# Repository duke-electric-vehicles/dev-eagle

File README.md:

# dev-eagle
Board files for Duke Electric Vehicles

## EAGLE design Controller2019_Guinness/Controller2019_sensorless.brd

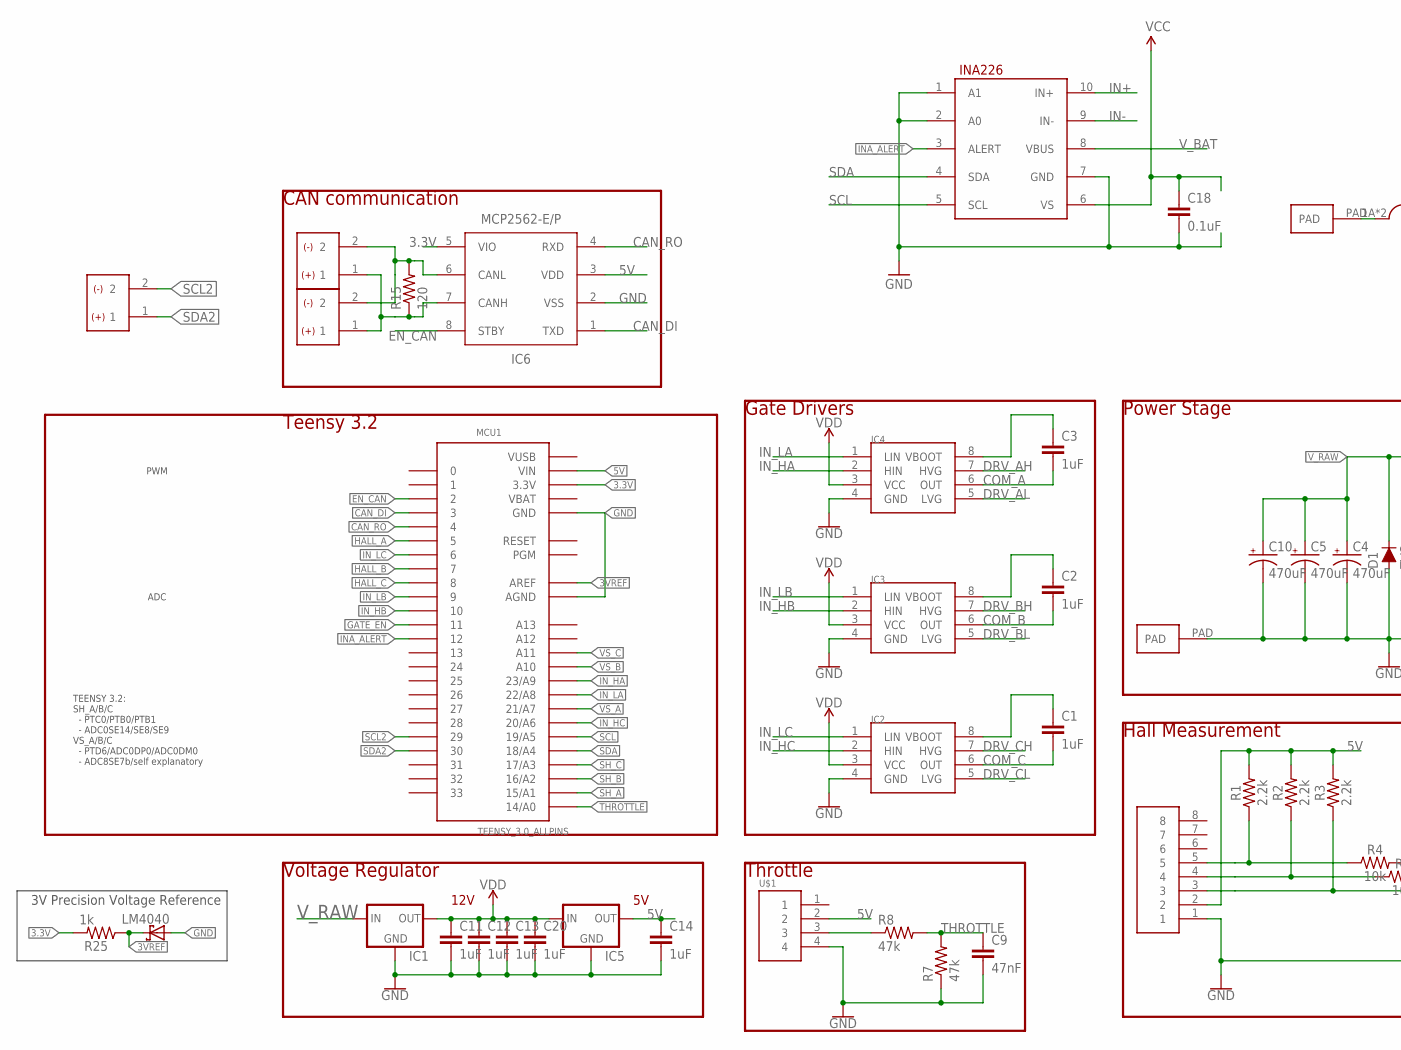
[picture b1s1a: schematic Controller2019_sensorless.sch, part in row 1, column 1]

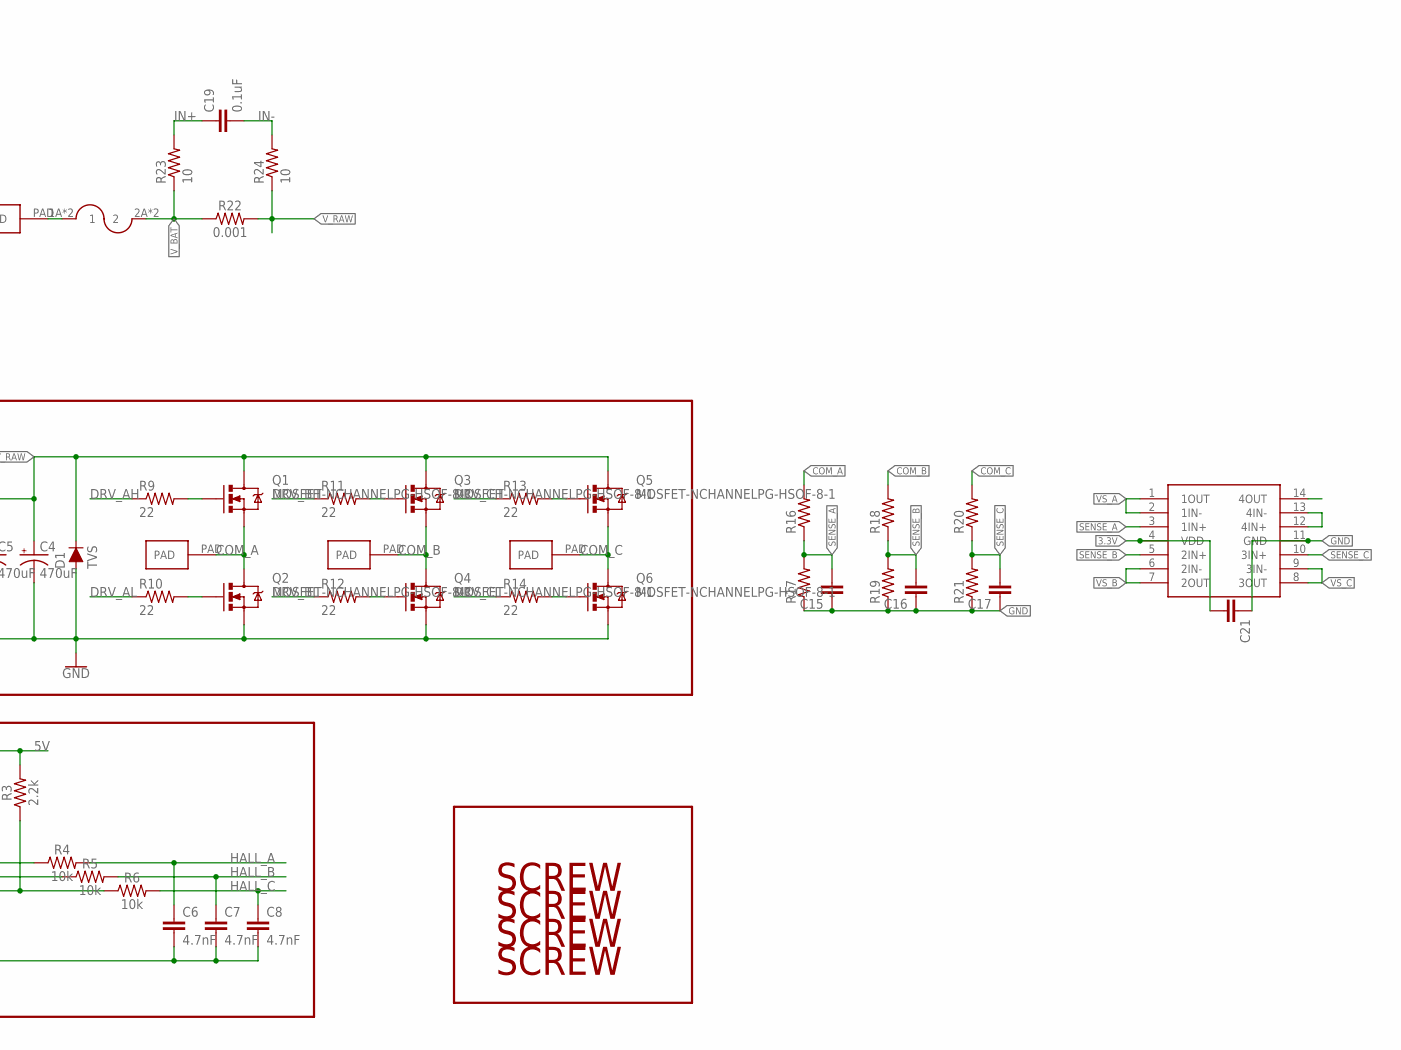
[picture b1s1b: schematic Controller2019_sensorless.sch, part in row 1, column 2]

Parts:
C1, C2, C3, C11, C12, C13, C14, C20: 1uF; CAP-PTH-SMALL-KIT
C4, C5, C10: 470uF; CPOL-RADIAL-5MM-10MM
C6, C7, C8: 4.7nF; 0603-CAP
C9: 47nF; 0603-CAP
C15, C16, C17, C21: CAP0603-CAP; 0603-CAP
C18, C19: 0.1uF; 0603-CAP
CAN1, CAN2: HEADER2; 2PINVALULOK
D1: TVS; DIODE-1N4001
I2C: HEADER2; 2PINVALULOK
IC1: V_REG_78XX; V78W_BACKWARDS
IC2, IC3, IC4: L6387EDIP8; DIP762W53P254L1092H508Q8B
IC5: V_REG_78XXV78W; V78W
IC6: MCP2562-E/P; PDIP8_300MC
IC7: INA226; PSOP-10
J3: FUSE; AUTO_FUSE
MCU1: TEENSY_3.0_ALLPINS
Q1, Q2, Q3, Q4, Q5, Q6: MOSFET-NCHANNELPG-HSOF-8-1; PG-HSOF-8-1
R1, R2, R3: 2.2k; 0603-RES
R4, R5, R6: 10k; 0603-RES
R7, R8: 47k; 0603-RES
R9, R10, R11, R12, R13, R14: 22; 0603-RES
R15: 120; 0603-RES
R16, R17, R18, R19, R20, R21: RESISTOR0603-RES; 0603-RES
R22: 0.001; R2512
R23, R24: 10; 0603-RES
R25: 1k; 0603-RES
U$1: HEADER4VALULOK; 4PINVALULOK
U$2: OPAMP_QUAD; TSSOP-14
U$4, U$5, U$6, U$7, U$8: PAD
U$10, U$11, U$12, U$13: SCREW; M3HOLE
U$14: HEADER8; 8PINVALULOK
U$15: LM4040; SOT23-3

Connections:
3.3V: C21.2, IC6.5 (VIO), MCU1.3.3V, MCU1.3.3V1 (3.3V), MCU1.3.3V2 (3.3V), R25.2, U$2.4 (VDD)
3VREF: MCU1.AREF, R25.1, U$15.1 (C)
5V: C14.1, IC5.OUT, IC6.3 (VDD), MCU1.VIN, R1.2, R2.2, R3.2, U$1.2, U$14.2
CANH: CAN1.1, CAN2.1, IC6.7 (CANH), R15.1
CANL: CAN1.2, CAN2.2, IC6.6 (CANL), R15.2
CAN_DI: IC6.1 (TXD), MCU1.3
CAN_RO: IC6.4 (RXD), MCU1.4
COM_A: C3.2, IC4.6 (OUT), Q1.S, Q2.D, R16.2, U$6.PAD
COM_B: C2.2, IC3.6 (OUT), Q3.S, Q4.D, R18.2, U$7.PAD
COM_C: C1.2, IC2.6 (OUT), Q5.S, Q6.D, R20.2, U$8.PAD
DRV_AH: IC4.7 (HVG), R9.1
DRV_AL: IC4.5 (LVG), R10.1
DRV_BH: IC3.7 (HVG), R11.1
DRV_BL: IC3.5 (LVG), R12.1
DRV_CH: IC2.7 (HVG), R13.1
DRV_CL: IC2.5 (LVG), R14.1
EN_CAN: IC6.8 (STBY), MCU1.2
GATE_EN: MCU1.11
GND: C4.-, C5.-, C6.2, C7.2, C8.2, C9.2, C10.-, C11.2, C12.2, C13.2, C14.2, C15.1, C16.1, C17.1, C18.2, C20.2, C21.1, D1.A, IC1.GND, IC2.4 (GND), IC3.4 (GND), IC4.4 (GND), IC5.GND, IC6.2 (VSS), IC7.1 (A1), IC7.2 (A0), IC7.7 (GND), MCU1.AGND, MCU1.GND, MCU1.GND1 (GND), MCU1.GND2 (GND), Q2.S, Q4.S, Q6.S, R7.1, R17.1, R19.1, R21.1, U$1.4, U$2.11 (GND), U$5.PAD, U$14.1, U$15.2 (A)
HALL_A: C6.1, MCU1.5, R4.2
HALL_B: C7.1, MCU1.7, R5.2
HALL_C: C8.1, MCU1.8, R6.2
IN+: C19.1, IC7.10 (IN+), R23.2
IN-: C19.2, IC7.9 (IN-), R24.2
INA_ALERT: IC7.3 (ALERT), MCU1.12
IN_HA: IC4.2 (HIN), MCU1.23/A9
IN_HB: IC3.2 (HIN), MCU1.10
IN_HC: IC2.2 (HIN), MCU1.20/A6
IN_LA: IC4.1 (LIN), MCU1.22/A8
IN_LB: IC3.1 (LIN), MCU1.9
IN_LC: IC2.1 (LIN), MCU1.6
unnamed: C1.1, IC2.8 (VBOOT)
unnamed: R3.1, R6.1, U$14.3
unnamed: C2.1, IC3.8 (VBOOT)
unnamed: R2.1, R5.1, U$14.4
unnamed: C3.1, IC4.8 (VBOOT)
unnamed: R1.1, R4.1, U$14.5
unnamed: R8.1, U$1.3
unnamed: Q1.G, R9.2
unnamed: Q2.G, R10.2
unnamed: Q3.G, R11.2
unnamed: Q4.G, R12.2
unnamed: Q5.G, R13.2
unnamed: Q6.G, R14.2
unnamed: U$2.12 (4IN+), U$2.13 (4IN-)
SCL: IC7.5 (SCL), MCU1.19/A5
SCL2: I2C.2, MCU1.29
SDA: IC7.4 (SDA), MCU1.18/A4
SDA2: I2C.1, MCU1.30
SENSE_A: C15.2, R16.1, R17.2, U$2.3 (1IN+)
SENSE_B: C16.2, R18.1, R19.2, U$2.5 (2IN+)
SENSE_C: C17.2, R20.1, R21.2, U$2.10 (3IN+)
SH_A: MCU1.15/A1
SH_B: MCU1.16/A2
SH_C: MCU1.17/A3
THROTTLE: C9.1, MCU1.14/A0, R7.2, R8.2
VBAT: MCU1.VBAT
VCC: C18.1, IC7.6 (VS)
VDD: C11.1, C12.1, C13.1, C20.1, IC1.OUT, IC2.3 (VCC), IC3.3 (VCC), IC4.3 (VCC), IC5.IN
VS_A: MCU1.21/A7, U$2.1 (1OUT), U$2.2 (1IN-)
VS_B: MCU1.A10, U$2.6 (2IN-), U$2.7 (2OUT)
VS_C: MCU1.A11, U$2.8 (3OUT), U$2.9 (3IN-)
VUSB: MCU1.VUSB
V_BAT: IC7.8 (VBUS), J3.2A (2), J3.2B (2), R22.1, R23.1
V_PREFUSE: J3.1A (1), J3.1B (1), U$4.PAD
V_RAW: C4.+, C5.+, C10.+, D1.C, IC1.IN, Q1.D, Q3.D, Q5.D, R22.2, R24.1

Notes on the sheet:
Power Stage
Hall Measurement
Gate Drivers
Throttle
Teensy 3.2
Voltage Regulator
12V
CAN communication
PWM
ADC
TEENSY 3.2: SH_A/B/C - PTC0/PTB0/PTB1 - ADC0SE14/SE8/SE9 VS_A/B/C - PTD6/ADC0DP0/ADC0DM0 - ADC8SE7b/self explanatory
3V Precision Voltage Reference

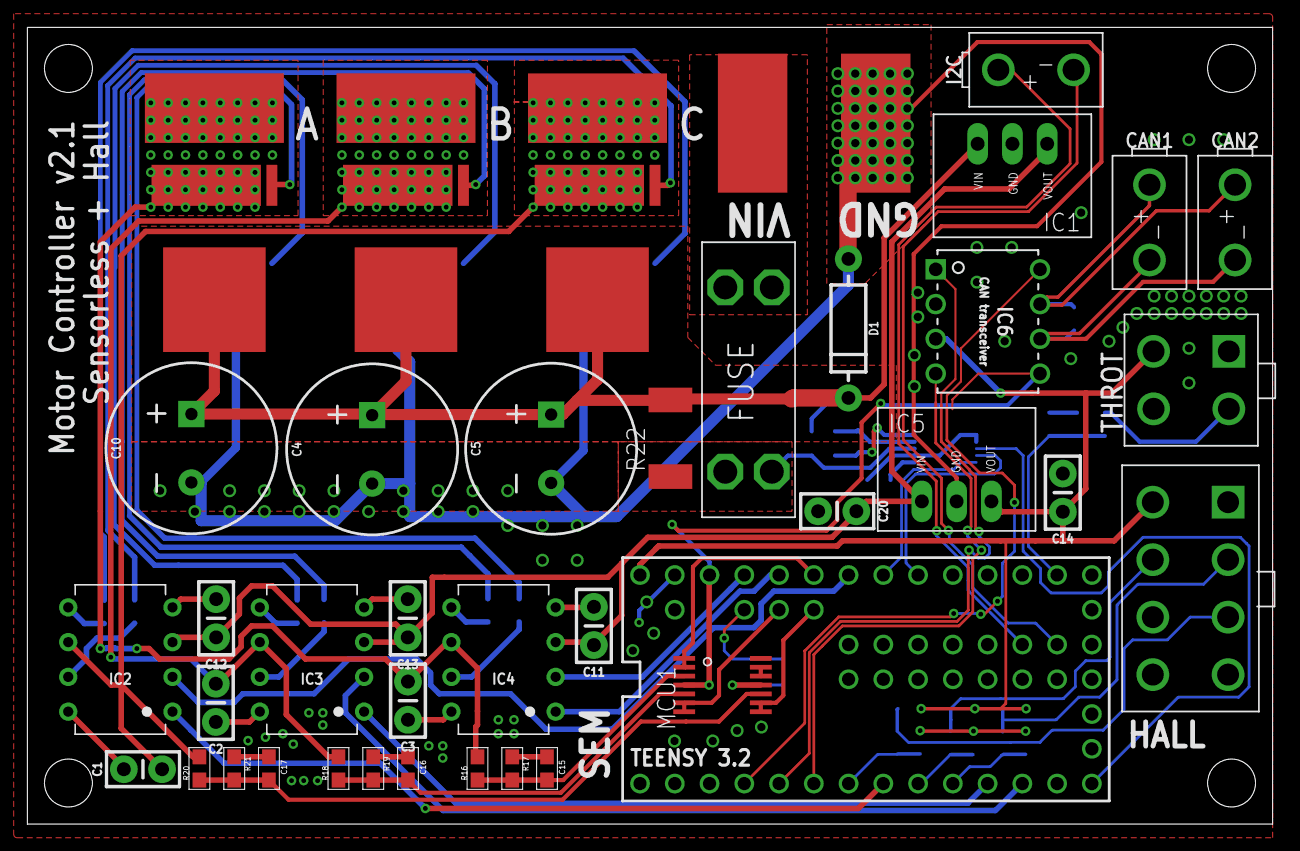
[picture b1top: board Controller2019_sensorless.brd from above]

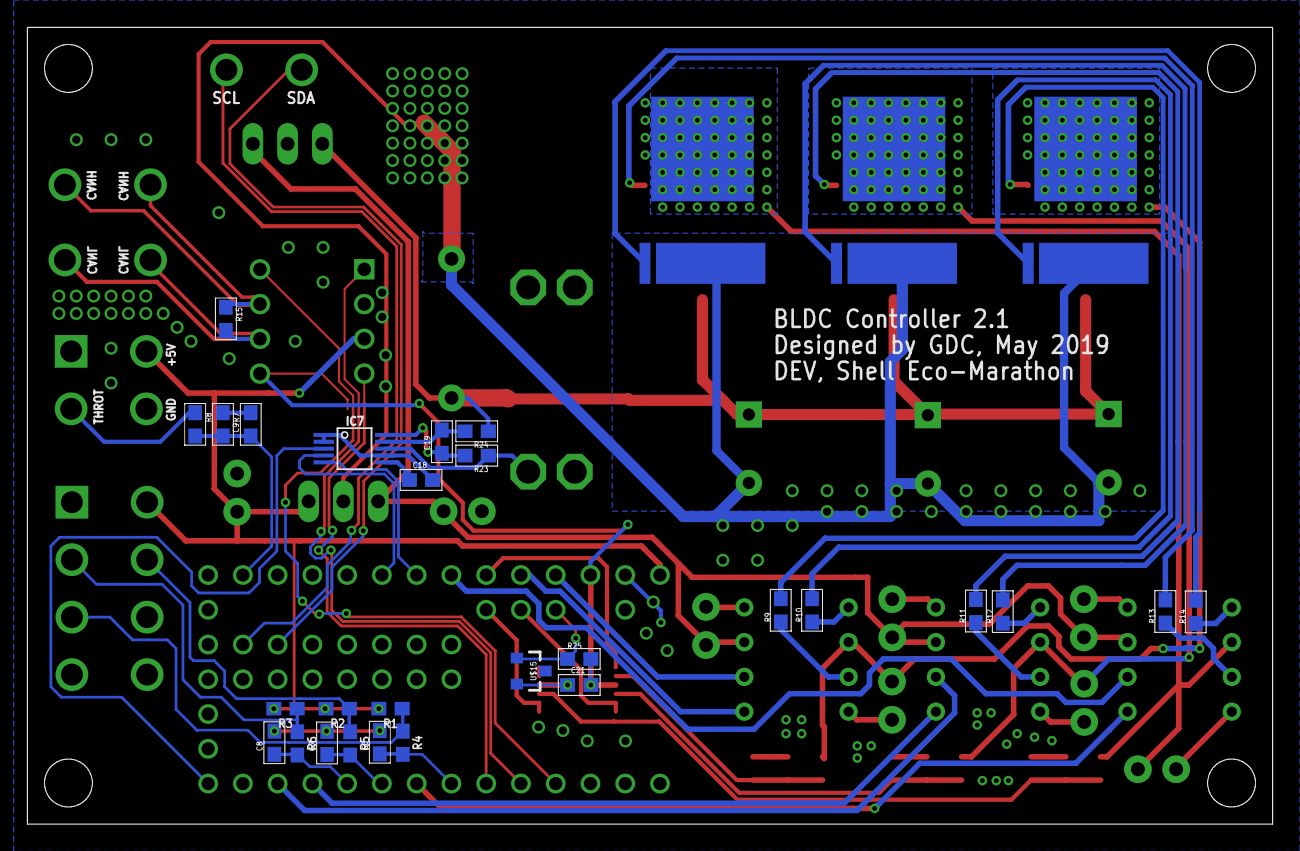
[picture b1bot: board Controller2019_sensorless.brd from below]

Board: 2 copper layers, 91.0 x 58.2 mm, 79 parts (31 on the bottom side), 60 nets.

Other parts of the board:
U$3: DEV

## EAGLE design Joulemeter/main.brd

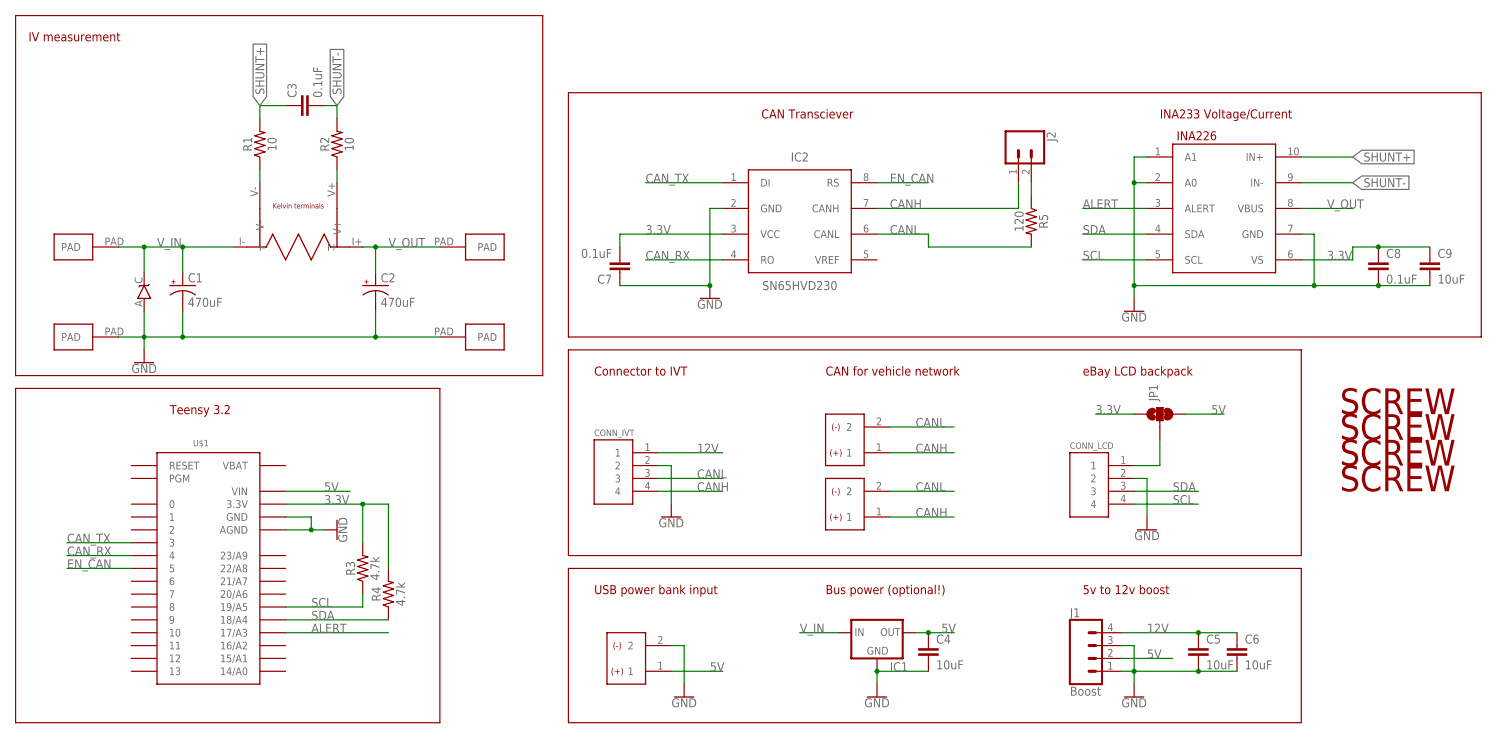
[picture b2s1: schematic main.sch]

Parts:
C1, C2: 470uF; CPOL-RADIAL-5MM-10MM
C3, C7, C8: 0.1uF; 0603
C4, C5, C6, C9: 10uF; 1210
CONN_IVT: LCD; 4PINVALULOK
CONN_LCD: LCD; 4PINVALULOK
IC1: V_REG_78XX; V78W_BACKWARDS
IC2: SN65HVD230; SOIC127P650X175-8
J1: Boost; 1X04_LONGPADS
J2: CONN_02; 1X02
JP1: JUMPER-SMT_3_1-NC_TRACE_SILK; SMT-JUMPER_3_1-NC_TRACE_SILK
R1, R2: 10; 0603
R3, R4: 4.7k; 0603
R5: 120; 0603
U$1: TEENSY_3.0_BASIC
U$2: 5mOhm; 2512_KELVIN
U$3, U$4, U$7, U$8: PAD
U$5: INA226; PSOP-10
U$6: TVS_UNIDO-214AC; DO-214AC
U$9, U$10: HEADER2; 2PINVALULOK
U$11, U$12, U$13, U$14: SCREW; M3HOLE
USB_PWR: USB_PWR; 2PINVALULOK

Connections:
3.3V: C7.2, C8.1, C9.1, IC2.3 (VCC), JP1.1, R3.2, R4.2, U$1.3.3V, U$1.3.3V1 (3.3V), U$5.6 (VS)
5V: C4.1, IC1.OUT, J1.2, JP1.3, U$1.VIN, USB_PWR.1
12V: C5.1, C6.1, CONN_IVT.1, J1.4
ALERT: U$1.17/A3, U$5.3 (ALERT)
CANH: CONN_IVT.4, IC2.7 (CANH), J2.1, U$9.1, U$10.1
CANL: CONN_IVT.3, IC2.6 (CANL), R5.2, U$9.2, U$10.2
CAN_RX: IC2.4 (RO), U$1.4
CAN_TX: IC2.1 (DI), U$1.3
EN_CAN: IC2.8 (RS), U$1.5
GND: C1.-, C2.-, C4.2, C5.2, C6.2, C7.1, C8.2, C9.2, CONN_IVT.2, CONN_LCD.2, IC1.GND, IC2.2 (GND), J1.1, J1.3, U$1.AGND, U$1.GND, U$1.GND1 (GND), U$4.PAD, U$5.1 (A1), U$5.2 (A0), U$5.7 (GND), U$6.A, U$8.PAD, USB_PWR.2
unnamed: R1.1, U$2.V-
unnamed: R2.1, U$2.V+
unnamed: CONN_LCD.1, JP1.2
unnamed: J2.2, R5.1
SCL: CONN_LCD.4, R3.1, U$1.19/A5, U$5.5 (SCL)
SDA: CONN_LCD.3, R4.1, U$1.18/A4, U$5.4 (SDA)
SHUNT+: C3.1, R1.2, U$5.10 (IN+)
SHUNT-: C3.2, R2.2, U$5.9 (IN-)
VBAT: U$1.VBAT
V_IN: C1.+, IC1.IN, U$2.I-, U$3.PAD, U$6.C
V_OUT: C2.+, U$2.I+, U$5.8 (VBUS), U$7.PAD

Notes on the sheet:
Bus power (optional!)
5v to 12v boost
USB power bank input
Connector to IVT
CAN for vehicle network
eBay LCD backpack
IV measurement
CAN Transciever
INA233 Voltage/Current
Teensy 3.2

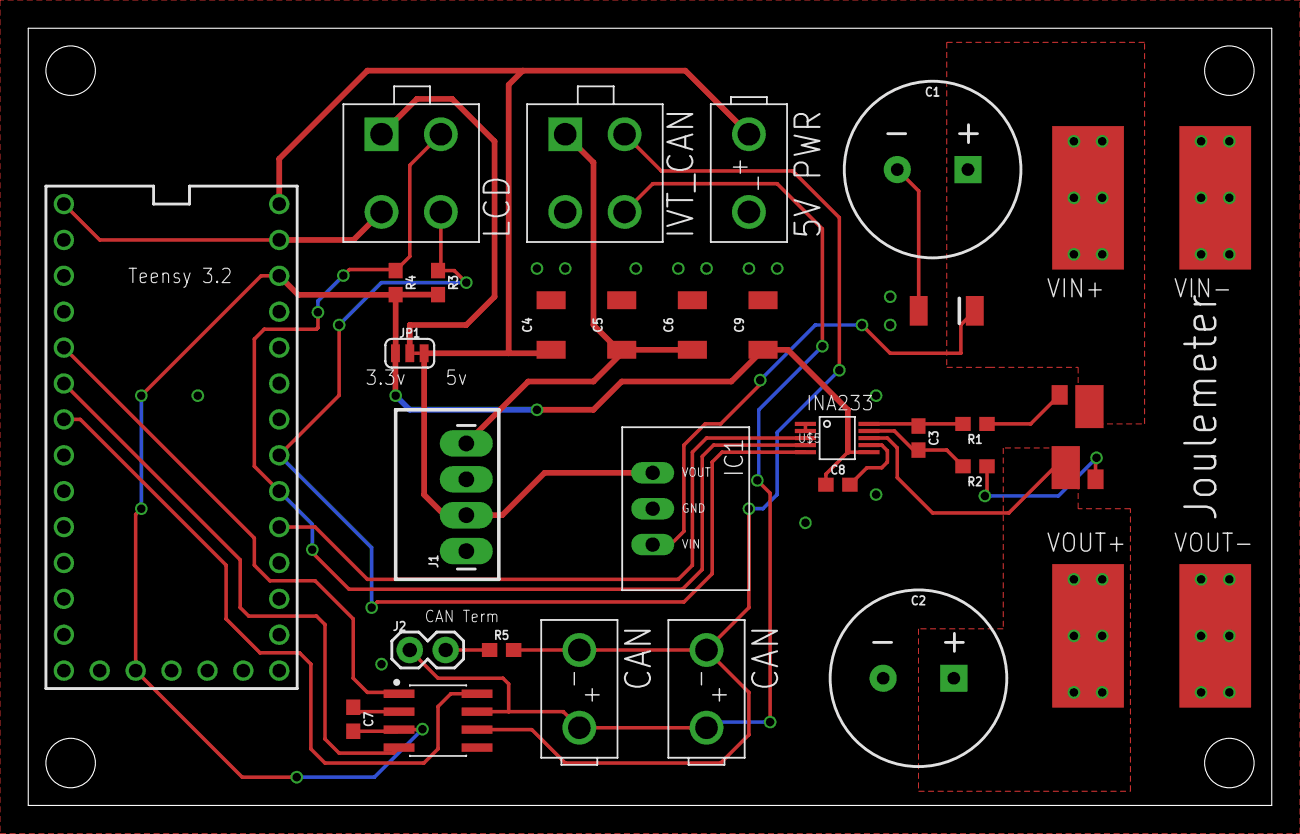
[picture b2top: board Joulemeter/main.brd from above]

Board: 2 copper layers, 88.0 x 55.0 mm, 36 parts (0 on the bottom side), 20 nets.

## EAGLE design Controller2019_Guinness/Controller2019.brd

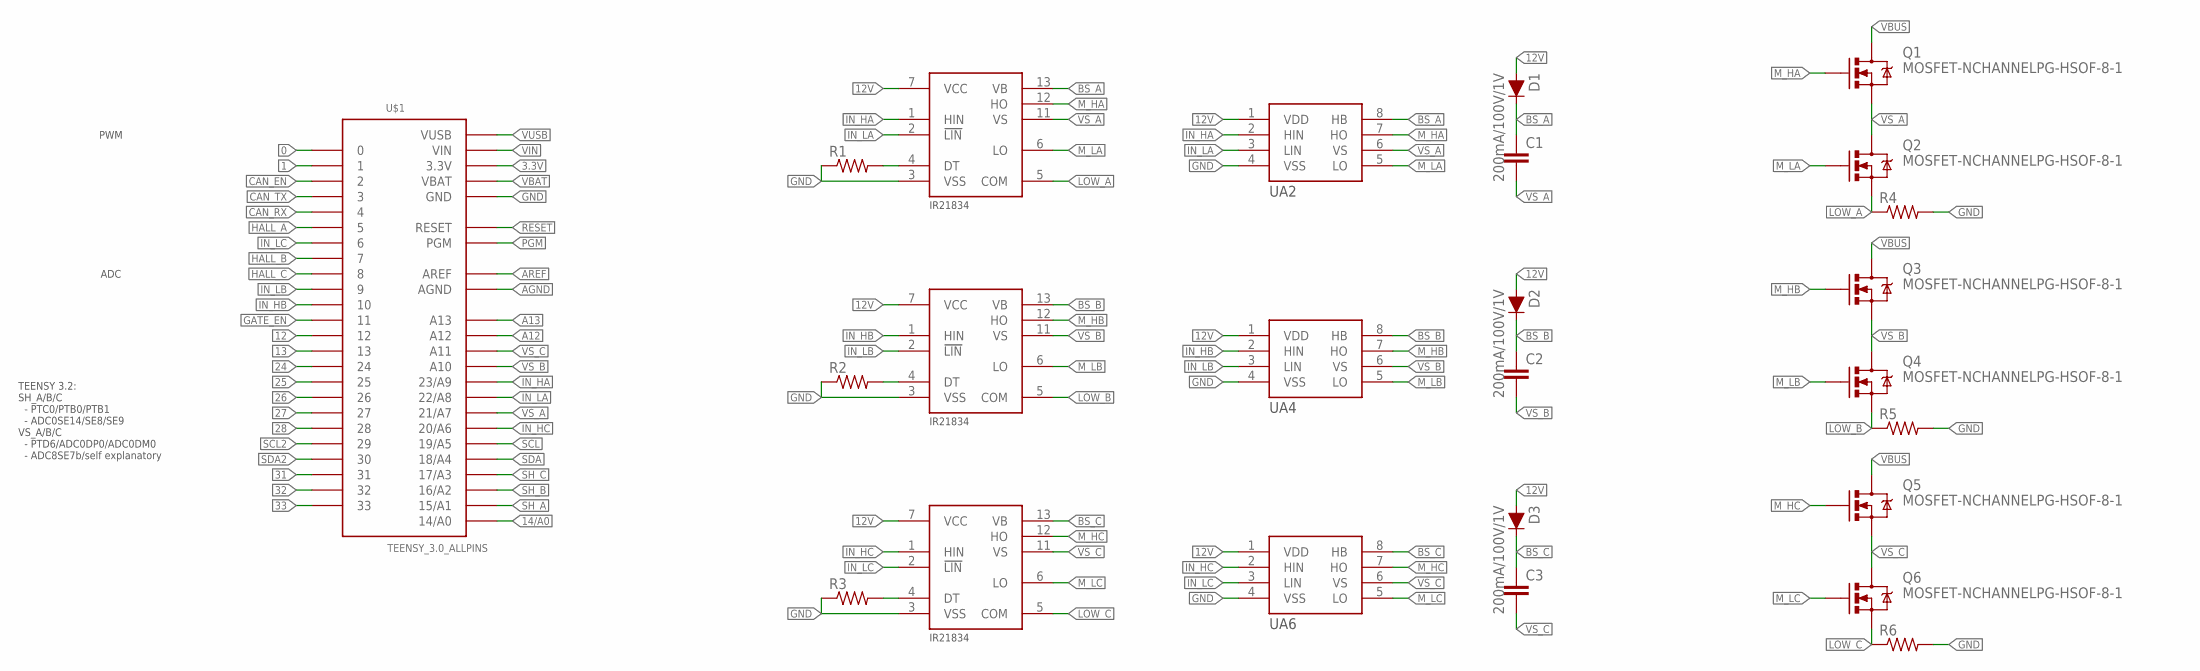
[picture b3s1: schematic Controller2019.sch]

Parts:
C1, C2, C3: CAP0603-CAP; 0603-CAP
D1, D2, D3: 200mA/100V/1V; DIODE-1N4148
Q1, Q2, Q3, Q4, Q5, Q6: MOSFET-NCHANNELPG-HSOF-8-1; PG-HSOF-8-1
R1, R2, R3: RESISTOR0603-RES; 0603-RES
R4, R5, R6: RESISTOR2512; R2512
U$1: TEENSY_3.0_ALLPINS
UA1, UA3, UA5: IR21834; SO14
UA2, UA4, UA6: GATEDRIVER_IND_ISL6700; SOIC8

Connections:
0: U$1.0
1: U$1.1
3.3V: U$1.3.3V, U$1.3.3V1 (3.3V), U$1.3.3V2 (3.3V)
12: U$1.12
12V: D1.A, D2.A, D3.A, UA1.7 (VCC), UA2.1 (VDD), UA3.7 (VCC), UA4.1 (VDD), UA5.7 (VCC), UA6.1 (VDD)
13: U$1.13
14/A0: U$1.14/A0
24: U$1.24
25: U$1.25
26: U$1.26
27: U$1.27
28: U$1.28
31: U$1.31
32: U$1.32
33: U$1.33
A12: U$1.A12
A13: U$1.A13
AGND: U$1.AGND
AREF: U$1.AREF
BS_A: C1.1, D1.C, UA1.13 (VB), UA2.8 (HB)
BS_B: C2.1, D2.C, UA3.13 (VB), UA4.8 (HB)
BS_C: C3.1, D3.C, UA5.13 (VB), UA6.8 (HB)
CAN_EN: U$1.2
CAN_RX: U$1.4
CAN_TX: U$1.3
GATE_EN: U$1.11
GND: R1.1, R2.1, R3.1, R4.2, R5.2, R6.2, U$1.GND, U$1.GND1 (GND), U$1.GND2 (GND), UA1.3 (VSS), UA2.4 (VSS), UA3.3 (VSS), UA4.4 (VSS), UA5.3 (VSS), UA6.4 (VSS)
HALL_A: U$1.5
HALL_B: U$1.7
HALL_C: U$1.8
IN_HA: U$1.23/A9, UA1.1 (HIN), UA2.2 (HIN)
IN_HB: U$1.10, UA3.1 (HIN), UA4.2 (HIN)
IN_HC: U$1.20/A6, UA5.1 (HIN), UA6.2 (HIN)
IN_LA: U$1.22/A8, UA1.2 (LIN), UA2.3 (LIN)
IN_LB: U$1.9, UA3.2 (LIN), UA4.3 (LIN)
IN_LC: U$1.6, UA5.2 (LIN), UA6.3 (LIN)
LOW_A: Q2.S, R4.1, UA1.5 (COM)
LOW_B: Q4.S, R5.1, UA3.5 (COM)
LOW_C: Q6.S, R6.1, UA5.5 (COM)
M_HA: Q1.G, UA1.12 (HO), UA2.7 (HO)
M_HB: Q3.G, UA3.12 (HO), UA4.7 (HO)
M_HC: Q5.G, UA5.12 (HO), UA6.7 (HO)
M_LA: Q2.G, UA1.6 (LO), UA2.5 (LO)
M_LB: Q4.G, UA3.6 (LO), UA4.5 (LO)
M_LC: Q6.G, UA5.6 (LO), UA6.5 (LO)
unnamed: R2.2, UA3.4 (DT)
unnamed: R3.2, UA5.4 (DT)
unnamed: R1.2, UA1.4 (DT)
PGM: U$1.PGM
RESET: U$1.RESET
SCL: U$1.19/A5
SCL2: U$1.29
SDA: U$1.18/A4
SDA2: U$1.30
SH_A: U$1.15/A1
SH_B: U$1.16/A2
SH_C: U$1.17/A3
VBAT: U$1.VBAT
VBUS: Q1.D, Q3.D, Q5.D
VIN: U$1.VIN
VS_A: C1.2, Q1.S, Q2.D, U$1.21/A7, UA1.11 (VS), UA2.6 (VS)
VS_B: C2.2, Q3.S, Q4.D, U$1.A10, UA3.11 (VS), UA4.6 (VS)
VS_C: C3.2, Q5.S, Q6.D, U$1.A11, UA5.11 (VS), UA6.6 (VS)
VUSB: U$1.VUSB

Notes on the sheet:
PWM
ADC
TEENSY 3.2: SH_A/B/C - PTC0/PTB0/PTB1 - ADC0SE14/SE8/SE9 VS_A/B/C - PTD6/ADC0DP0/ADC0DM0 - ADC8SE7b/self explanatory

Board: 2 copper layers, 25 parts (0 on the bottom side), 28 nets, no tracks yet.

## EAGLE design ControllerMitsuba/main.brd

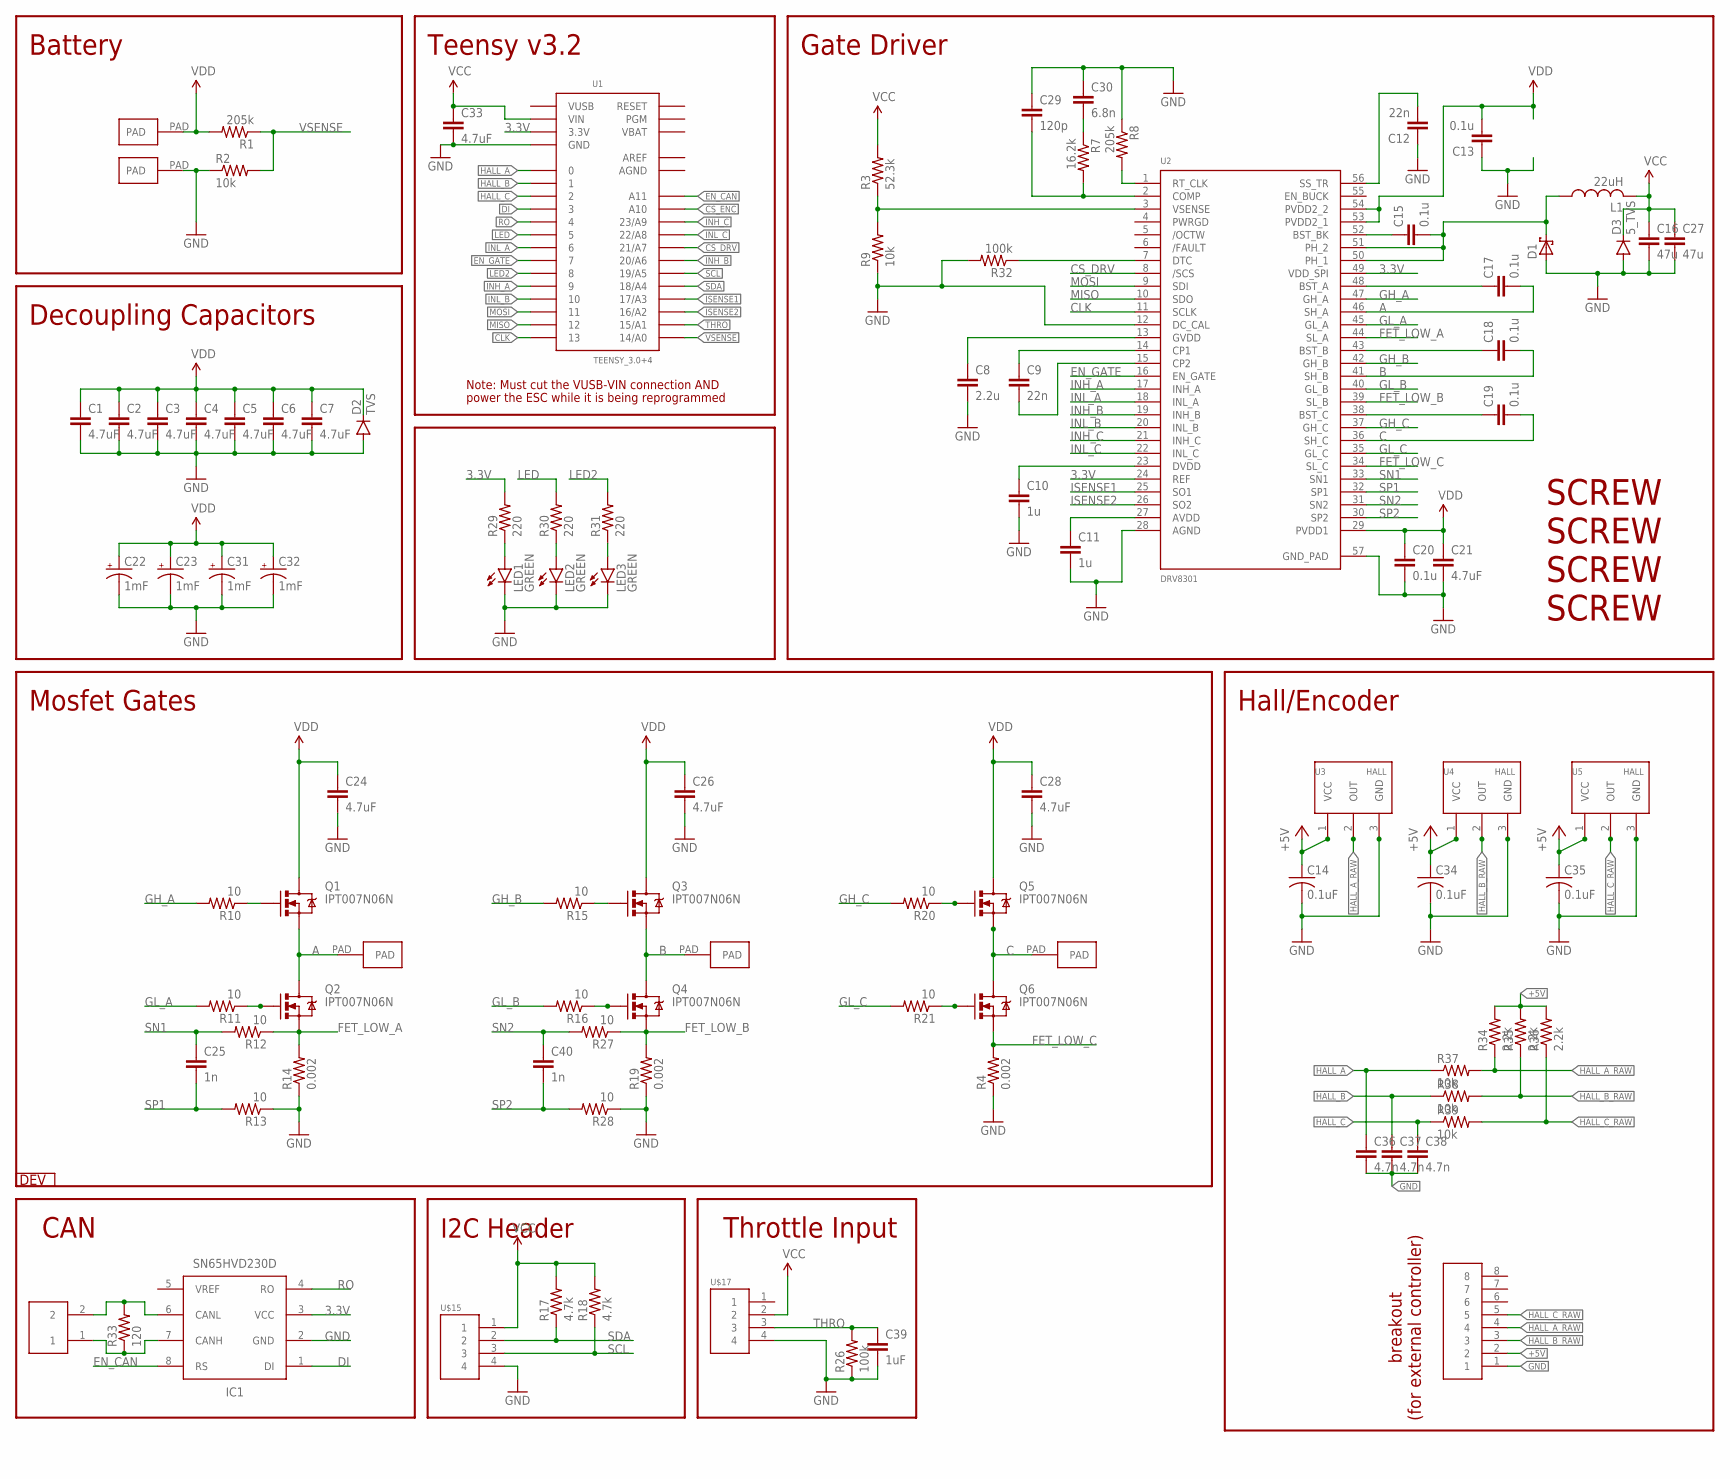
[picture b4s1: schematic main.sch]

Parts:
C1, C2, C3, C4, C5, C6, C7, C21, C24, C26, C28, C33: 4.7uF; 1206
C8: 2.2u; 0603-CAP
C9, C12: 22n; 0603-CAP
C10, C11: 1u; 0603-CAP
C13, C15, C17, C18, C19, C20: 0.1u; 0603-CAP
C14, C34, C35: 0.1uF; C0603
C16, C27: 47u; 0805
C22, C23, C31, C32: 1mF; CAPPRD508W65D1275H3100B
C25, C40: 1n; 0603-CAP
C29: 120p; 0603-CAP
C30: 6.8n; 0603-CAP
C36, C37, C38: 4.7n; 0603-CAP
C39: 1uF; 0603-CAP
CAN: HEADER2; 2PINVALULOK
D1: SCHOTTKY_SMA; SMA
D2: TVS; SMC
D3: 5_TVS; SOT23-3
IC1: SN65HVD230D; SO-8
L1: 22uH; L5650M
LED1, LED2, LED3: GREEN; LED-1206
Q1, Q2, Q3, Q4, Q5, Q6: IPT007N06N; PG-HSOF-8-1
R1, R8: 205k; 0603-RES
R2, R9, R37, R38, R39: 10k; 0603-RES
R3: 52.3k; 0603-RES
R4, R14, R19: 0.002; R2512
R7: 16.2k; 0603-RES
R10, R11, R12, R13, R15, R16, R20, R21, R27, R28: 10; 0603-RES
R17, R18: 4.7k; 0603-RES
R26, R32: 100k; 0603-RES
R29, R30, R31: 220; 0603-RES
R33: 120; 0603-RES
R34, R35, R36: 2.2k; 0603-RES
U1: TEENSY_3.0+4
U2: DRV8301
U3, U4, U5: HALLSOT23W; SOT23W
U$15, U$17: HEADER4VALULOK; 4PINVALULOK
U$16: DEV
U$19, U$20, U$21, U$22: SCREW; M3HOLE
U$23, U$24, U$25, U$26, U$27: PAD
U$29: HEADER8; 8PINVALULOK

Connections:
3.3V: IC1.3 (VCC), R29.2, U1.3.3V, U1.3.3V1 (3.3V), U2.24 (REF), U2.49 (VDD_SPI)
+5V: C14.1, C34.1, C35.1, R34.2, R35.2, R36.2, U3.1 (VCC), U4.1 (VCC), U5.1 (VCC), U$29.2
A: C17.2, Q1.S, Q2.D, U2.46 (SH_A), U$23.PAD
AGND: U1.AGND
AREF: U1.AREF
B: C18.2, Q3.S, Q4.D, U2.41 (SH_B), U$24.PAD
C: C19.2, Q5.S, Q6.D, U2.36 (SH_C), U$25.PAD
CANH: CAN.1, IC1.7 (CANH), R33.1
CANL: CAN.2, IC1.6 (CANL), R33.2
CLK: U1.13, U2.11 (SCLK)
CS_DRV: U1.21/A7, U2.8 (/SCS)
CS_ENC: U1.A10
DI: IC1.1 (DI), U1.3
EN_CAN: IC1.8 (RS), U1.A11
EN_GATE: U1.7, U2.16 (EN_GATE)
FET_LOW_A: Q2.S, R12.1, R14.2, U2.44 (SL_A)
FET_LOW_B: Q4.S, R19.2, R27.1, U2.39 (SL_B)
FET_LOW_C: Q6.S, R4.2, U2.34 (SL_C)
GH_A: R10.2, U2.47 (GH_A)
GH_B: R15.2, U2.42 (GH_B)
GH_C: R20.2, U2.37 (GH_C)
GL_A: R11.2, U2.45 (GL_A)
GL_A': Q2.G, R11.1
GL_B: R16.2, U2.40 (GL_B)
GL_B': Q4.G, R16.1
GL_C: R21.2, U2.35 (GL_C)
GL_C': Q6.G, R21.1
GND: C1.2, C2.2, C3.2, C4.2, C5.2, C6.2, C7.2, C8.2, C10.2, C11.2, C12.1, C13.1, C14.2, C16.2, C20.2, C21.2, C22.-, C23.-, C24.2, C26.2, C27.2, C28.2, C29.1, C30.1, C31.-, C32.-, C33.2, C34.2, C35.2, C36.2, C37.2, C38.2, C39.2, D1.A, D2.A, D3.1 (A), IC1.2 (GND), LED1.C, LED2.C, LED3.C, R2.1, R4.1, R8.1, R9.1, R13.1, R14.1, R19.1, R26.1, R28.1, R32.2, U1.GND, U1.GND1 (GND), U2.12 (DC_CAL), U2.28 (AGND), U2.57 (GND_PAD), U3.3 (GND), U4.3 (GND), U5.3 (GND), U$15.4, U$17.4, U$27.PAD, U$29.1
HALL_A: C36.1, R37.1, U1.0
HALL_A_RAW: R34.1, R37.2, U3.2 (OUT), U$29.4
HALL_B: C37.1, R38.1, U1.1
HALL_B_RAW: R35.1, R38.2, U4.2 (OUT), U$29.3
HALL_C: C38.1, R39.1, U1.2
HALL_C_RAW: R36.1, R39.2, U5.2 (OUT), U$29.5
INH_A: U1.9, U2.17 (INH_A)
INH_B: U1.20/A6, U2.19 (INH_B)
INH_C: U1.23/A9, U2.21 (INH_C)
INL_A: U1.6, U2.18 (INL_A)
INL_B: U1.10, U2.20 (INL_B)
INL_C: U1.22/A8, U2.22 (INL_C)
ISENSE1: U1.17/A3, U2.25 (SO1)
ISENSE2: U1.16/A2, U2.26 (SO2)
LED: R30.2, U1.5
LED2: R31.2, U1.8
MISO: U1.12, U2.10 (SDO)
MOSI: U1.11, U2.9 (SDI)
unnamed: Q3.G, R15.1
unnamed: R3.1, R9.2, U2.3 (VSENSE)
unnamed: C29.2, R7.2, U2.2 (COMP)
unnamed: C10.1, U2.23 (DVDD)
unnamed: Q5.G, R20.1
unnamed: C12.2, U2.56 (SS_TR)
unnamed: C30.2, R7.1
unnamed: C15.1, U2.52 (BST_BK)
unnamed: Q1.G, R10.1
unnamed: R8.2, U2.1 (RT_CLK)
unnamed: LED1.A, R29.1
unnamed: R32.1, U2.7 (DTC)
unnamed: LED2.A, R30.1
unnamed: LED3.A, R31.1
unnamed: C19.1, U2.38 (BST_C)
unnamed: C9.1, U2.14 (CP1)
unnamed: C11.1, U2.27 (AVDD)
unnamed: C9.2, U2.15 (CP2)
unnamed: C8.1, U2.13 (GVDD)
unnamed: C18.1, U2.43 (BST_B)
unnamed: C17.1, U2.48 (BST_A)
unnamed: C15.2, D1.C, L1.1, U2.50 (PH_1), U2.51 (PH_2)
RO: IC1.4 (RO), U1.4
SCL: R18.1, U1.19/A5, U$15.3
SDA: R17.1, U1.18/A4, U$15.2
SN1: C25.1, R12.2, U2.33 (SN1)
SN2: C40.1, R27.2, U2.31 (SN2)
SP1: C25.2, R13.2, U2.32 (SP1)
SP2: C40.2, R28.2, U2.30 (SP2)
THRO: C39.1, R26.2, U1.15/A1, U$17.3
VBAT: U1.VBAT
VCC: C16.1, C27.1, C33.1, D3.3 (C), L1.2, R3.2, R17.2, R18.2, U1.VIN, U$15.1, U$17.2
VDD: C1.1, C2.1, C3.1, C4.1, C5.1, C6.1, C7.1, C13.2, C20.1, C21.1, C22.+, C23.+, C24.1, C26.1, C28.1, C31.+, C32.+, D2.C, Q1.D, Q3.D, Q5.D, R1.2, U2.29 (PVDD1), U2.53 (PVDD2_1), U2.54 (PVDD2_2), U$26.PAD
VSENSE: R1.1, R2.2, U1.14/A0
VUSB: U1.VUSB

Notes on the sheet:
Teensy v3.2
Gate Driver
Mosfet Gates
Battery
Hall/Encoder
Decoupling Capacitors
Note: Must cut the VUSB-VIN connection AND
power the ESC while it is being reprogrammed
Throttle Input
I2C Header
CAN
breakout (for external controller)

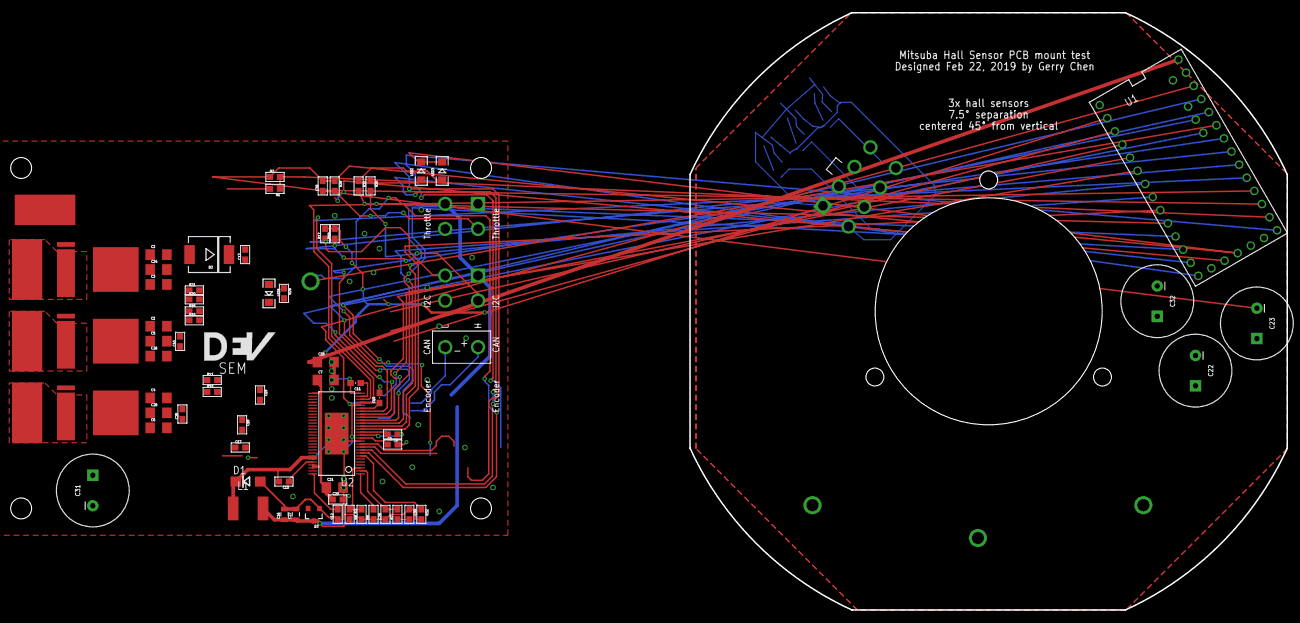
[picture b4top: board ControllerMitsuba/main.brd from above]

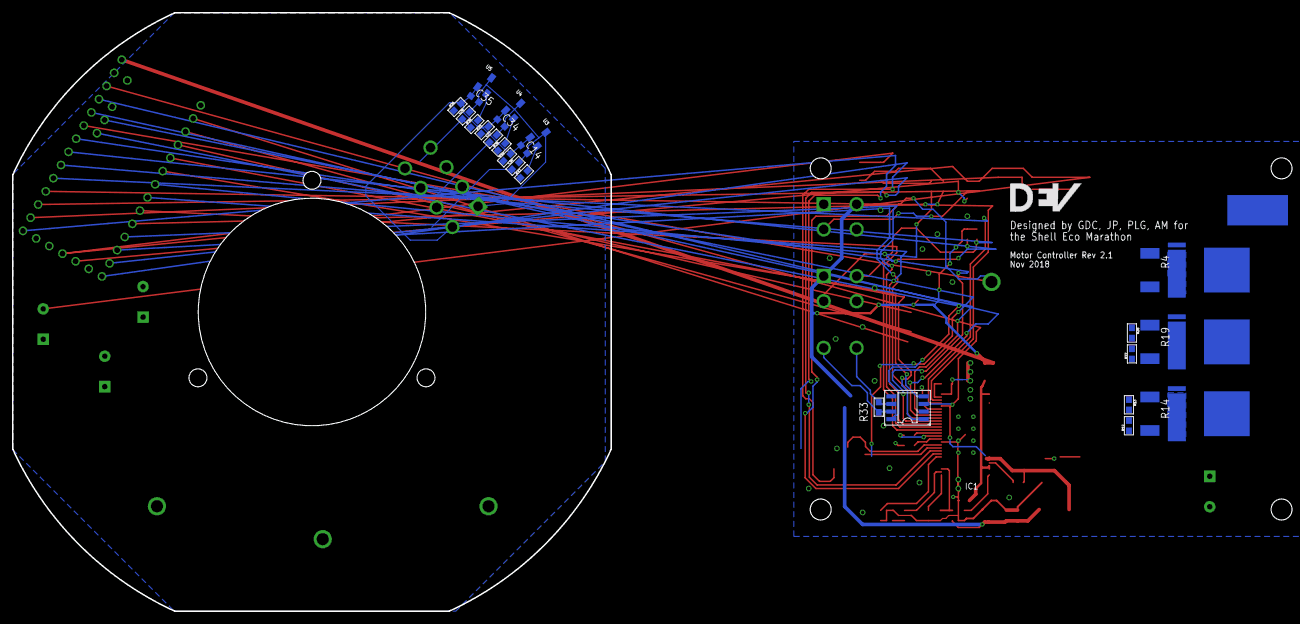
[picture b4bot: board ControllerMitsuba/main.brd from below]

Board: 2 copper layers, 109 parts (29 on the bottom side), 76 nets.

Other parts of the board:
U$28: DEV
U$30, U$31: DEV

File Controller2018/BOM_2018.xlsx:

Description | Digikey Part # | Value | Components | Price | Qty | Total |  | Grand total | 70.48
Teensy 3.2 | 1568-1231-ND |  | U1 | 22.5 | 1 | 22.5 | yes
DRV8301 | 296-29433-1-ND |  | U2 | 6.14 | 1 | 6.14 | yes
NFET | NVMFS5C404NLAFT1GOSCT-ND |  | Q1 Q2 Q3 Q4 Q5 Q6 | 3.47 | 6 | 20.82 | yes
TVS | 497-6522-1-ND | 48V | D2 | 0.53 | 1 | 0.53 | yes
TVS | GSOT05-E3-08CT-ND | 5v | D3 | 0.38 | 1 | 0.38 | yes
Quad Op-apm | 296-11968-1-ND |  |  | 2.0099999999999998 | 1 | 2.0099999999999998
PFET | 785-1001-1-ND |  |  | 0.48 | 1 | 0.48
 |  |  |  |  |  | 0
LED 1206 | 160-1456-1-ND | Green | LED1 LED2 LED3 | 0.34 | 3 | 1.02 | yes
Ceramic cap 50V 0603 | 490-1429-1-ND | 120pF | C29 | 0.01 | 1 | 0.01
Ceramic cap 50V 0603 | 399-1089-1-ND | 6.8nF | C30 | 0.01 | 1 | 0.01
Resistor 0603 | 311-16.2KHRCT-ND | 16.2k | R7 | 0.01 | 1 | 0.01
Resistor 0603 | 311-52.3KHRCT-ND | 52.3k | R3 | 0.01 | 1 | 0.01 | yes
Inductor | 587-2952-1-ND | 22uH | L1 | 0.43 | 1 | 0.43 | yes
Ceramic cap 6.3V 0805 | 311-1897-1-ND | 47uF | C16 C27 | 0.46 | 2 | 0.92
Schottkey diode | 641-1701-1-ND | 200V 3A | D1 | 0.43 | 1 | 0.43 | yes
Ceramic cap 16V 0603 | 490-3296-1-ND | 2.2uF | C8 | 0.1 | 1 | 0.1
Ceramic cap 50V 0603 | 490-1500-6-ND | 22nF | C9 C12 | 0.01 | 2 | 0.02 | yes
Ceramic cap 50V 0603 | 490-1519-6-ND | 0.1uF | C13 C15 C17 C18 C19 C20 C22 C23 | 0.01 | 8 | 0.08 | yes
Ceramic cap 25V 0805 | 490-3335-6-ND | 4.7uF | C14 C21 C35 | 0.1 | 3 | 0.30000000000000004
Ceramic cap 25V 0603 | 490-6339-6-ND | 10nF | C36 C37 C38 | 0.01 | 3 | 0.03
Resistor 0603 | 311-1.00KHRCT-ND | 1k | R5 R6 R25 | 0.01 | 3 | 0.03 | yes
Ceramic cap 50V 0603 | 587-3247-1-ND | 1uF | C10 C11 C39 | 0.12 | 3 | 0.36 | yes
Resistor 0603 | 311-4.70KHRCT-ND | 4.7k | R17 R18 | 0.01 | 2 | 0.02
Ceramic cap 50V 0603 | 478-1215-1-ND | 1nF | C25 | 0.01 | 1 | 0.01 | yes
Resistor 2512 | CSNL2512FT2L00DKR-ND | 2m | R4 R14 R19 | 0.53 | 3 | 1.59 | yes
Resistor 0603 | 311-10.0HRCT-ND | 10 | R10 R11 R12 R13 R15 R16 R20 R21 | 0.01 | 8 | 0.08 | yes
Resistor 0603 | 311-10.0KHRCT-ND | 10k | R2 R4 R9 R22 R23 R24 | 0.01 | 6 | 0.06 | yes
Resistor 0603 | 311-205KHRCT-ND | 205k | R1 R8 R26 | 0.01 | 3 | 0.03 | yes
Ceramic cap 50V 1206 | 587-2994-1-ND | 4.7uF | C1 C2 C3 C4 C5 C6 C7 C24 C26 C28 C33 | 0.15 | 11 | 1.65 | yes
Aluminum cap | 565-4618-ND | 1000uF | C22 C23 C31 C32 | 2.14 | 4 | 8.56 | yes
Resistor 0603 | 311-220HRCT-ND | 220 | R29 R30 R31 | 0.01 | 3 | 0.03
 |  |  |  |  |  | 0
VAL-U-LOK header | A30605-ND | 8 pin |  | 0.71 | 1 | 0.71 | yes
VAL-U-LOK header | A30603-ND | 4 pin |  | 0.56000000000000005 | 2 | 1.1200000000000001 | yes
 |  |  |  |  |  | 0
 |  |  |  |  |  | 0
 |  |  |  |  |  | 0
 |  |  |  |  |  | 0
 |  |  |  |  |  | 0
 |  |  |  |  |  | 0
 |  |  |  |  |  | 0
 |  |  |  |  |  | 0
 |  |  |  |  |  | 0
 |  |  |  |  |  | 0
 |  |  |  |  |  | 0
 |  |  |  |  |  | 0
 |  |  |  |  |  | 0
 |  |  |  |  |  | 0
 |  |  |  |  |  | 0
 |  |  |  |  |  | 0

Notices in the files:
parts and their libraries:
SparkFun-Capacitors: Licensing: Creative Commons ShareAlike 4.0 International - https://creativecommons.org/licenses/by-sa/4.0
PowerMagnetics: Copyright: Würth Elektronik
